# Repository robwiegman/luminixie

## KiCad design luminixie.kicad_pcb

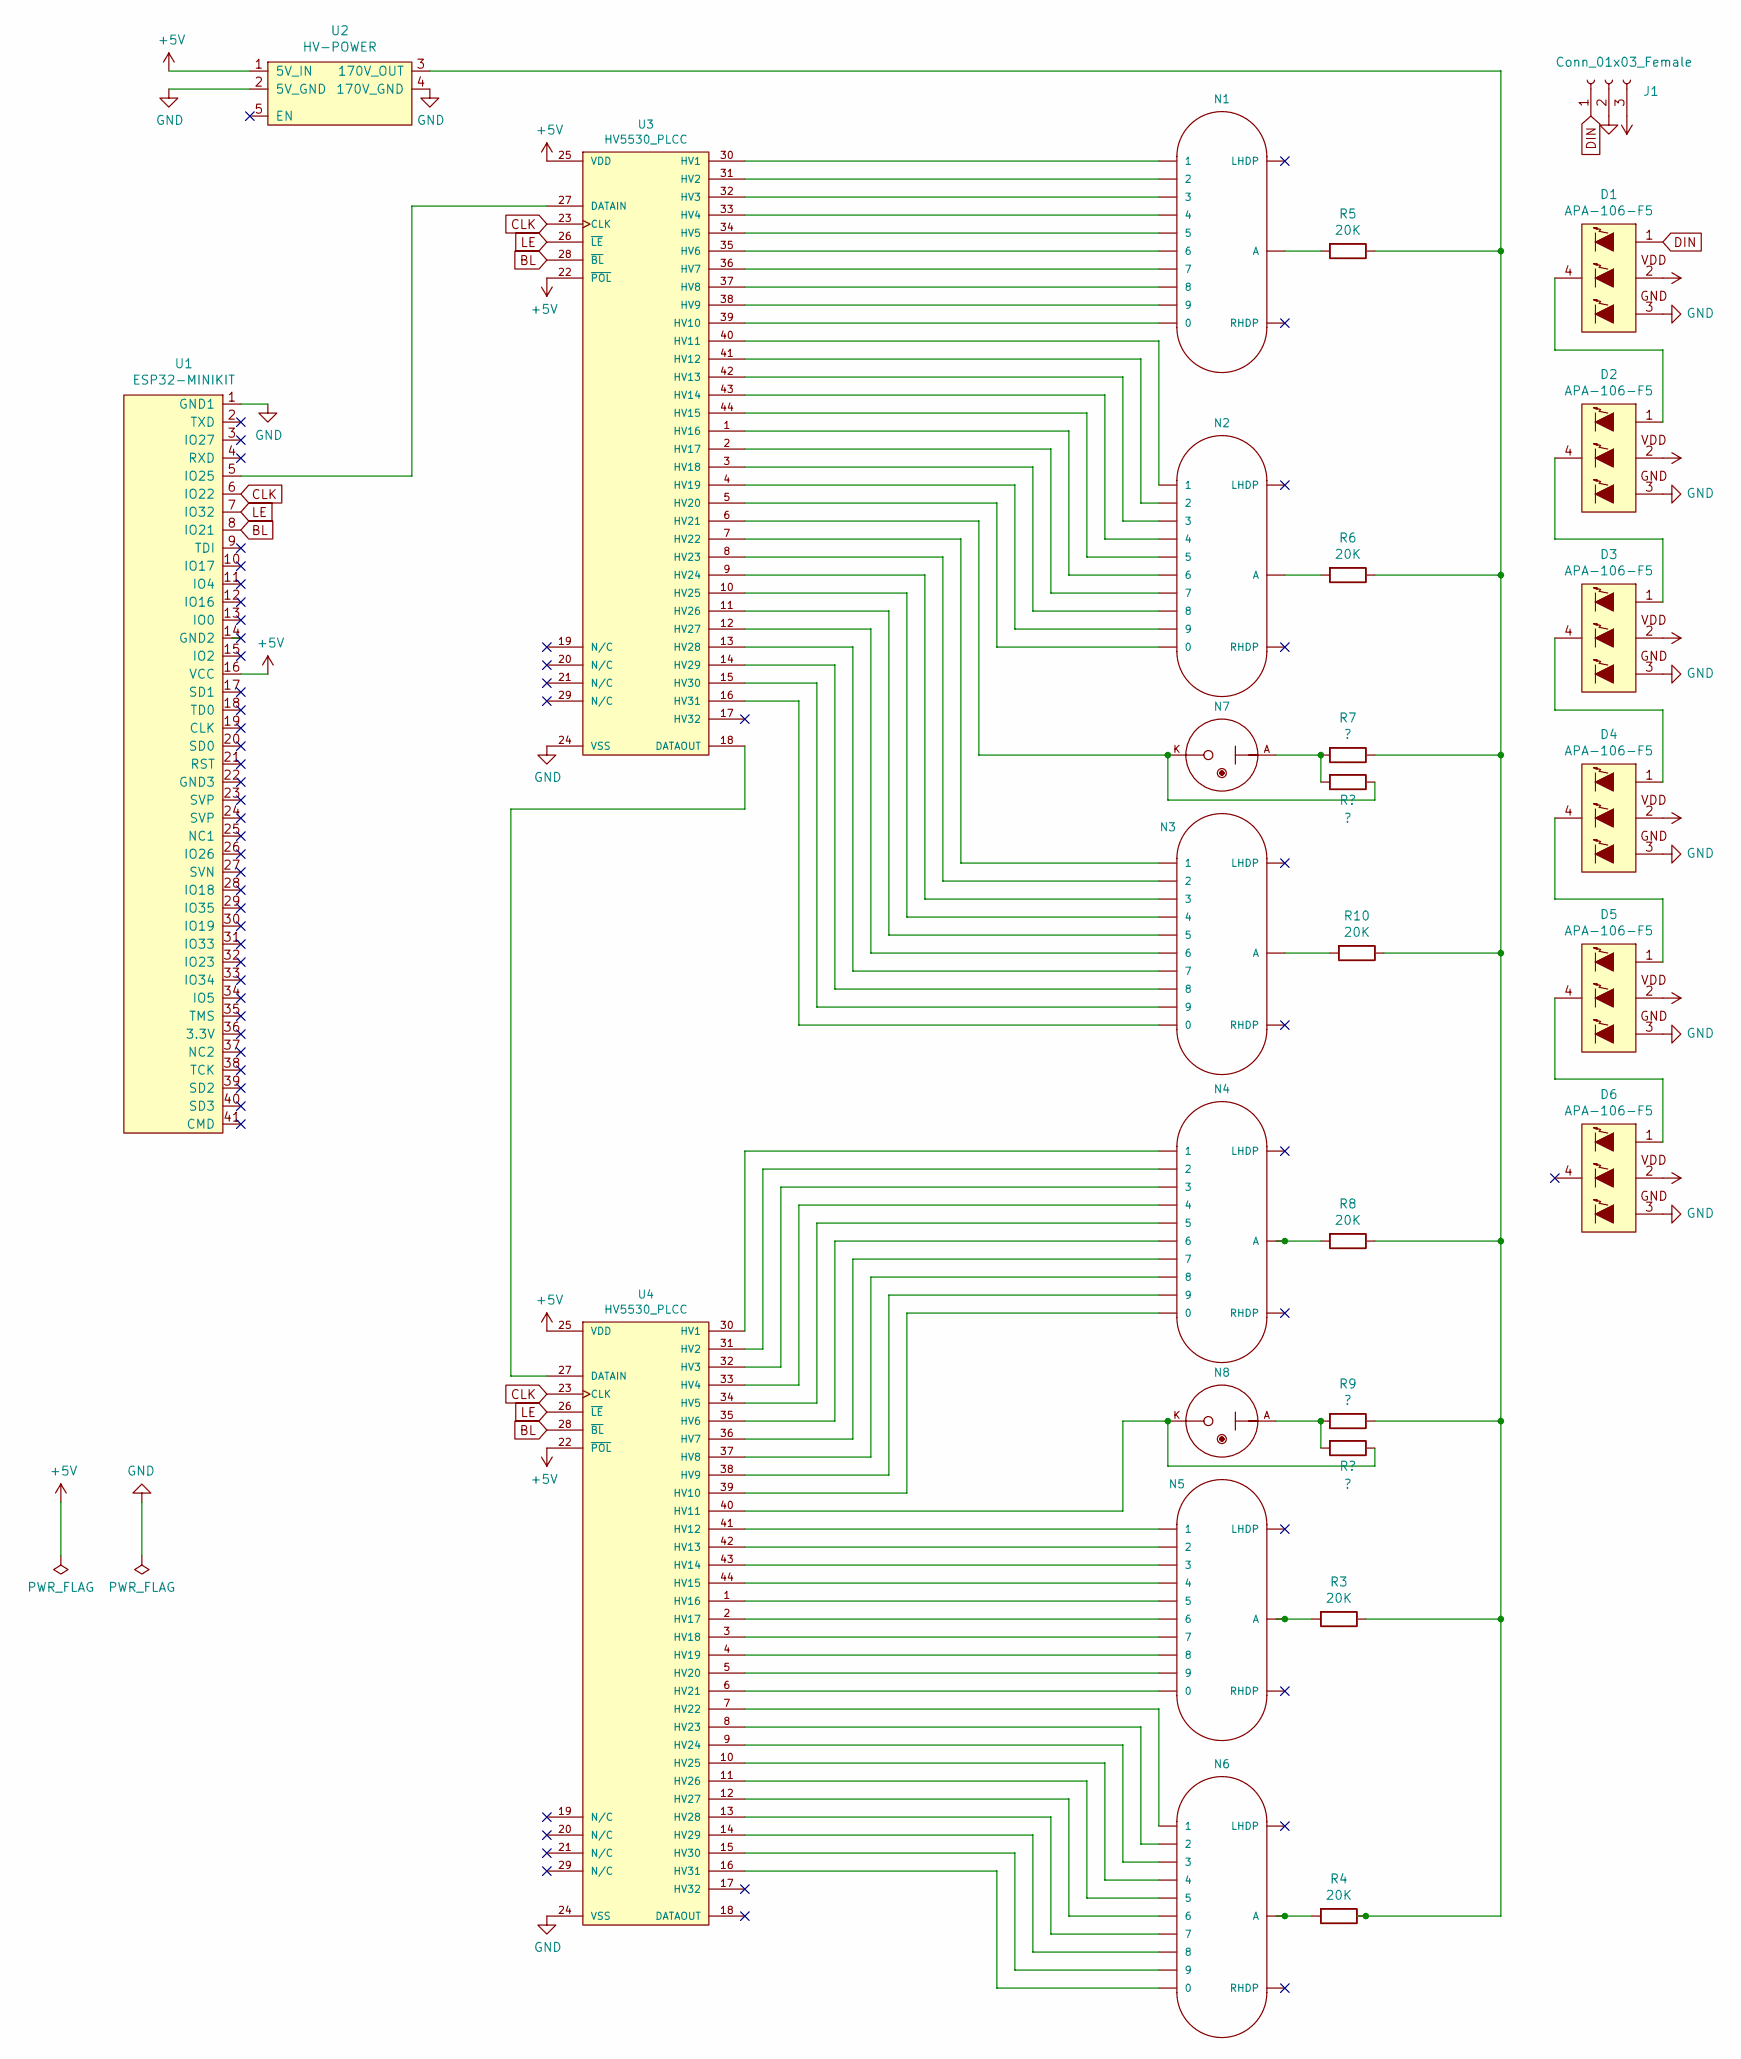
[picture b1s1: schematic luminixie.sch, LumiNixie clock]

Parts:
D1, D2, D3, D4, D5, D6: APA-106-F5; APA-106-F8
J1: Conn_01x03_Female; PinHeader_1x03_P2.54mm_Vertical
N1, N2, N3, N4, N5, N6: IN-14; nixies-us-IN-14
N7, N8: IN-3; nixies-us-IN-3
R3, R4, R5, R6, R8, R10: 20K; R_Axial_DIN0207_L6.3mm_D2.5mm_P7.62mm_Horizontal
R7, R9: ?; R_Axial_DIN0207_L6.3mm_D2.5mm_P7.62mm_Horizontal
U1: ESP32-MINIKIT; PinHeader_1x06_P2.54mm_Vertical
U2: HV-POWER; PinHeader_1x03_P2.54mm_Vertical
U3, U4: HV5530_PLCC; PLCC-44_THT-Socket

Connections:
+5V: D1.2 (VDD), D2.2 (VDD), D3.2 (VDD), D4.2 (VDD), D5.2 (VDD), D6.2 (VDD), J1.3, U1.16 (VCC), U2.1 (5V_IN), U3.22 (~POL), U3.25 (VDD), U4.22 (~POL), U4.25 (VDD)
BL: U1.8 (IO21), U3.28 (~BL), U4.28 (~BL)
CLK: U1.6 (IO22), U3.23 (CLK), U4.23 (CLK)
DIN: D1.1 (DIN), J1.1
GND: D1.3 (GND), D2.3 (GND), D3.3 (GND), D4.3 (GND), D5.3 (GND), D6.3 (GND), J1.2, U1.1 (GND1), U2.2 (5V_GND), U2.4 (170V_GND), U3.24 (VSS), U4.24 (VSS)
LE: U1.7 (IO32), U3.26 (~LE), U4.26 (~LE)
unnamed: D1.4 (DOUT), D2.1 (DIN)
unnamed: D2.4 (DOUT), D3.1 (DIN)
unnamed: D3.4 (DOUT), D4.1 (DIN)
unnamed: D4.4 (DOUT), D5.1 (DIN)
unnamed: D5.4 (DOUT), D6.1 (DIN)
unnamed: N1.0, U3.39 (HV10)
unnamed: N1.1, U3.30 (HV1)
unnamed: N1.2, U3.31 (HV2)
unnamed: N1.3, U3.32 (HV3)
unnamed: N1.4, U3.33 (HV4)
unnamed: N1.5, U3.34 (HV5)
unnamed: N1.6, U3.35 (HV6)
unnamed: N1.7, U3.36 (HV7)
unnamed: N1.8, U3.37 (HV8)
unnamed: N1.9, U3.38 (HV9)
unnamed: N1.A, R5.2
unnamed: N2.0, U3.5 (HV20)
unnamed: N2.1, U3.40 (HV11)
unnamed: N2.2, U3.41 (HV12)
unnamed: N2.3, U3.42 (HV13)
unnamed: N2.4, U3.43 (HV14)
unnamed: N2.5, U3.44 (HV15)
unnamed: N2.6, U3.1 (HV16)
unnamed: N2.7, U3.2 (HV17)
unnamed: N2.8, U3.3 (HV18)
unnamed: N2.9, U3.4 (HV19)
unnamed: N2.A, R6.2
unnamed: N3.0, U3.16 (HV31)
unnamed: N3.1, U3.7 (HV22)
unnamed: N3.2, U3.8 (HV23)
unnamed: N3.3, U3.9 (HV24)
unnamed: N3.4, U3.10 (HV25)
unnamed: N3.5, U3.11 (HV26)
unnamed: N3.6, U3.12 (HV27)
unnamed: N3.7, U3.13 (HV28)
unnamed: N3.8, U3.14 (HV29)
unnamed: N3.9, U3.15 (HV30)
unnamed: N3.A, R10.2
unnamed: N4.0, U4.39 (HV10)
unnamed: N4.1, U4.30 (HV1)
unnamed: N4.2, U4.31 (HV2)
unnamed: N4.3, U4.32 (HV3)
unnamed: N4.4, U4.33 (HV4)
unnamed: N4.5, U4.34 (HV5)
unnamed: N4.6, U4.35 (HV6)
unnamed: N4.7, U4.36 (HV7)
unnamed: N4.8, U4.37 (HV8)
unnamed: N4.9, U4.38 (HV9)
unnamed: N4.A, R8.2
unnamed: N5.0, U4.6 (HV21)
unnamed: N5.1, U4.41 (HV12)
unnamed: N5.2, U4.42 (HV13)
unnamed: N5.3, U4.43 (HV14)
unnamed: N5.4, U4.44 (HV15)
unnamed: N5.5, U4.1 (HV16)
unnamed: N5.6, U4.2 (HV17)
unnamed: N5.7, U4.3 (HV18)
unnamed: N5.8, U4.4 (HV19)
unnamed: N5.9, U4.5 (HV20)
unnamed: N5.A, R3.2
unnamed: N6.0, U4.16 (HV31)
unnamed: N6.1, U4.7 (HV22)
unnamed: N6.2, U4.8 (HV23)
unnamed: N6.3, U4.9 (HV24)
unnamed: N6.4, U4.10 (HV25)
unnamed: N6.5, U4.11 (HV26)
unnamed: N6.6, U4.12 (HV27)
unnamed: N6.7, U4.13 (HV28)
unnamed: N6.8, U4.14 (HV29)
unnamed: N6.9, U4.15 (HV30)
unnamed: N6.A, R4.2
unnamed 90: N7.A, R7.2; also elsewhere on the board
unnamed 91: N7.K, U3.6 (HV21); also elsewhere on the board
unnamed 92: N8.A, R9.2; also elsewhere on the board
unnamed 93: N8.K, U4.40 (HV11); also elsewhere on the board
unnamed: R3.1, R4.1, R5.1, R6.1, R7.1, R8.1, R9.1, R10.1, U2.3 (170V_OUT)
unnamed: U1.5 (IO25), U3.27 (DATAIN)
unnamed: U3.18 (DATAOUT), U4.27 (DATAIN)

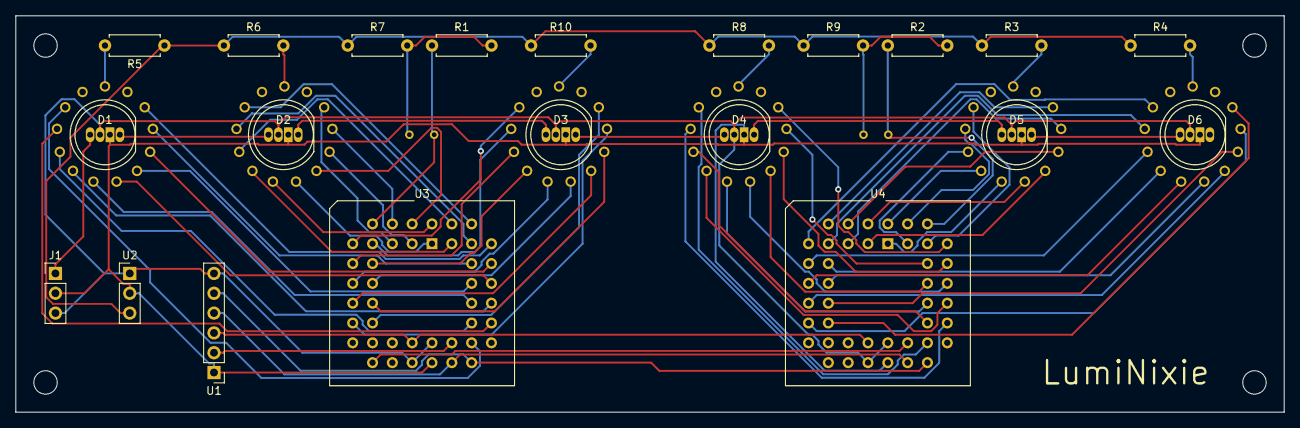
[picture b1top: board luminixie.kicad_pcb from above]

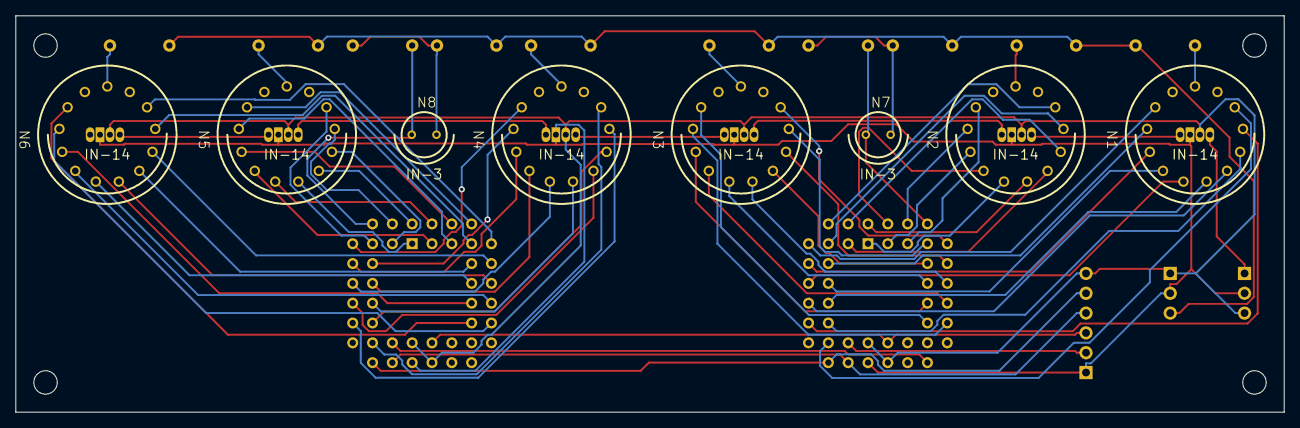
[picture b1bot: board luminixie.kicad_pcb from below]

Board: 2 copper layers, 162.6 x 50.8 mm, 33 parts (8 on the bottom side), 84 nets.

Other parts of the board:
R1, R2: ?; R_Axial_DIN0207_L6.3mm_D2.5mm_P7.62mm_Horizontal
REF1, REF2, REF5, REF6: MountingHole_3mm

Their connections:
unnamed 90: R1.2; also elsewhere on the board
unnamed 91: R1.1; also elsewhere on the board
unnamed 92: R2.2; also elsewhere on the board
unnamed 93: R2.1; also elsewhere on the board

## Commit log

2019-09-24 Add drillholes, add Luminixie logo, add edge cuts, delete netlist, add dependencies (apa-106, nixies)
2019-09-24 Set local clearance for apa-106 to suppress DRC error
2019-09-24 Add project specific libraries
2019-09-29 Voltage divider for IN-3
2019-10-02 Move labels of nixies on silk layers, so that they have no overlap with drill holes
2019-11-07 Add Gerbers
2019-11-30 Moved pcb to own subdirectory, add subdirectory for Arduino code
2019-12-01 Add ability to show date
2019-12-01 Add README.md to Arduino
2019-12-01 Add temperature and humidity sensor
2019-12-02 Add support for IN-3 dots
2019-12-02 Disable NTP updates when in AP mode
2019-12-06 Add alternative AntiCathodePoisoningSequence
2019-12-12 Add frontend
2019-12-12 Add container element
2019-12-12 Layout
2019-12-15 Add fallback JS, improved UI
2019-12-15 Name change
2019-12-17 Add nixie tube display setting to UI
2019-12-17 Never light all tubes + dots at once (it sometimes causes issues with the power supply)
2019-12-21 Add ability to configure time-dots-mode
2019-12-21 Remove subdirectories because SPIFFS file names can be 32 bytes max (see https://github.com/me-no-dev/arduino-esp32fs-plugin/issues/3)
2019-12-31 Add configurable led-mode, add led-mode "Rainbow"
2019-12-31 Add knight rider led mode, speed up runAntiCathodePoisoningSequence2
2020-01-02 Speed up antiCathodePoisoningSequence, only send changed brightness to leds, add NewYears ritual
